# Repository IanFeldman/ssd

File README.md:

# ssd
2025 Cal Poly EE/CPE senior project exploring nonvolatile flash storage. Includes a [prototype design](#nor-prototype-2) using an 8051 and small NOR flash IC and the [final design](#nand-final) with a modern Atmel microcontroller and multiple high-density NAND flash ICs on a custom PCB.

## nand-final
2Gib NAND flash memory board with virtual serial interface over USB. Supports default and RAID 1 configurations.

### Firmware Build and Flash Instructions (Linux)
```sh
# Install dependencies
sudo apt install gcc-avr avr-libc avrdude make

# Clone this repo
git clone https://github.com/IanFeldman/ssd.git
cd ssd/nand-final/firmware

# Burn fuses (first time only)
make fuses

# Compile and flash firmware using ISP
# (edit makefile as needed)
make [UART=1] [RAID=1] # Optionally enable UART debugging or RAID 1
make flash
```

UART debugging interferes with some NAND chip control lines. Enable it at your own risk.\
RAID is performed across all 4 chips, so it decreases the address space fourfold.

### Usage:
Plug PCB into PC USB port and open a terminal with:\
```screen /dev/[path-to-usb-device] -b 9600```

### Commands:
<table>

<tr>
<td>Command</td>
<td>Usage</td>
<td>Function</td>
</tr>
<tr>
<td>Help</td>
<td>
  
```help```
</td>
<td>Displays device info and a list of commands.</td>
</tr>
<tr>
<td>Read</td>
<td>
  
```read 0x[row] 0x[column] [size]```
</td>
<td>Reads [size] bytes from memory.<br>A device will not read across a page boundary.</td>
</tr>
<tr>
<td>Write</td>
<td>
  
```write 0x[row] 0x[column] 0x[data]```
</td>
<td>Writes a single byte [data] to memory.</td>
</tr>
<tr>
<td>Erase</td>
<td>
  
```erase 0x[row]```
</td>
<td>Erases a block from memory.</td>
</tr>
</table>

Note:
- ```[row]``` is three bytes and represents a page address. Max value: 0x0FFFFF (0x040000 with RAID enabled).
- ```[column]``` is two bytes and represents a page offset in bytes. Max value: 0x07FF.
- ```[data]``` is one byte.
- ```[size]``` is a decimal unsigned integer.

## nor-prototype-2
Prototype breadboard 512kB flash memory storage device. Interface over UART at 9600 baud. Compile with SDCC and program with avrdude. See hardware schematic for hardware details.

### Firmware Build and Flash Instructions (Linux)
```sh
# Install dependencies
sudo apt install sdcc

# Clone this repo
git clone https://github.com/IanFeldman/ssd.git
cd ssd/nor-prototype-2/firmware

# Compile and flash firmware using ISP
make
./program.sh
```

### Usage:
Connect a serial cable to ```RXD``` and ```TXD``` on the microcontroller. Open a terminal with:\
```screen /dev/[path-to-serial-cable] -b 9600```

### Commands:
- Read an address ```r[address]```
- Erase an address ```e[address]```
- Program an address ```p[address][data]```

Where:
- ```[address]``` is 3 hex bytes
- ```[data]``` is one hex byte

## nor-prototype-1
Flash memory controller prototype.

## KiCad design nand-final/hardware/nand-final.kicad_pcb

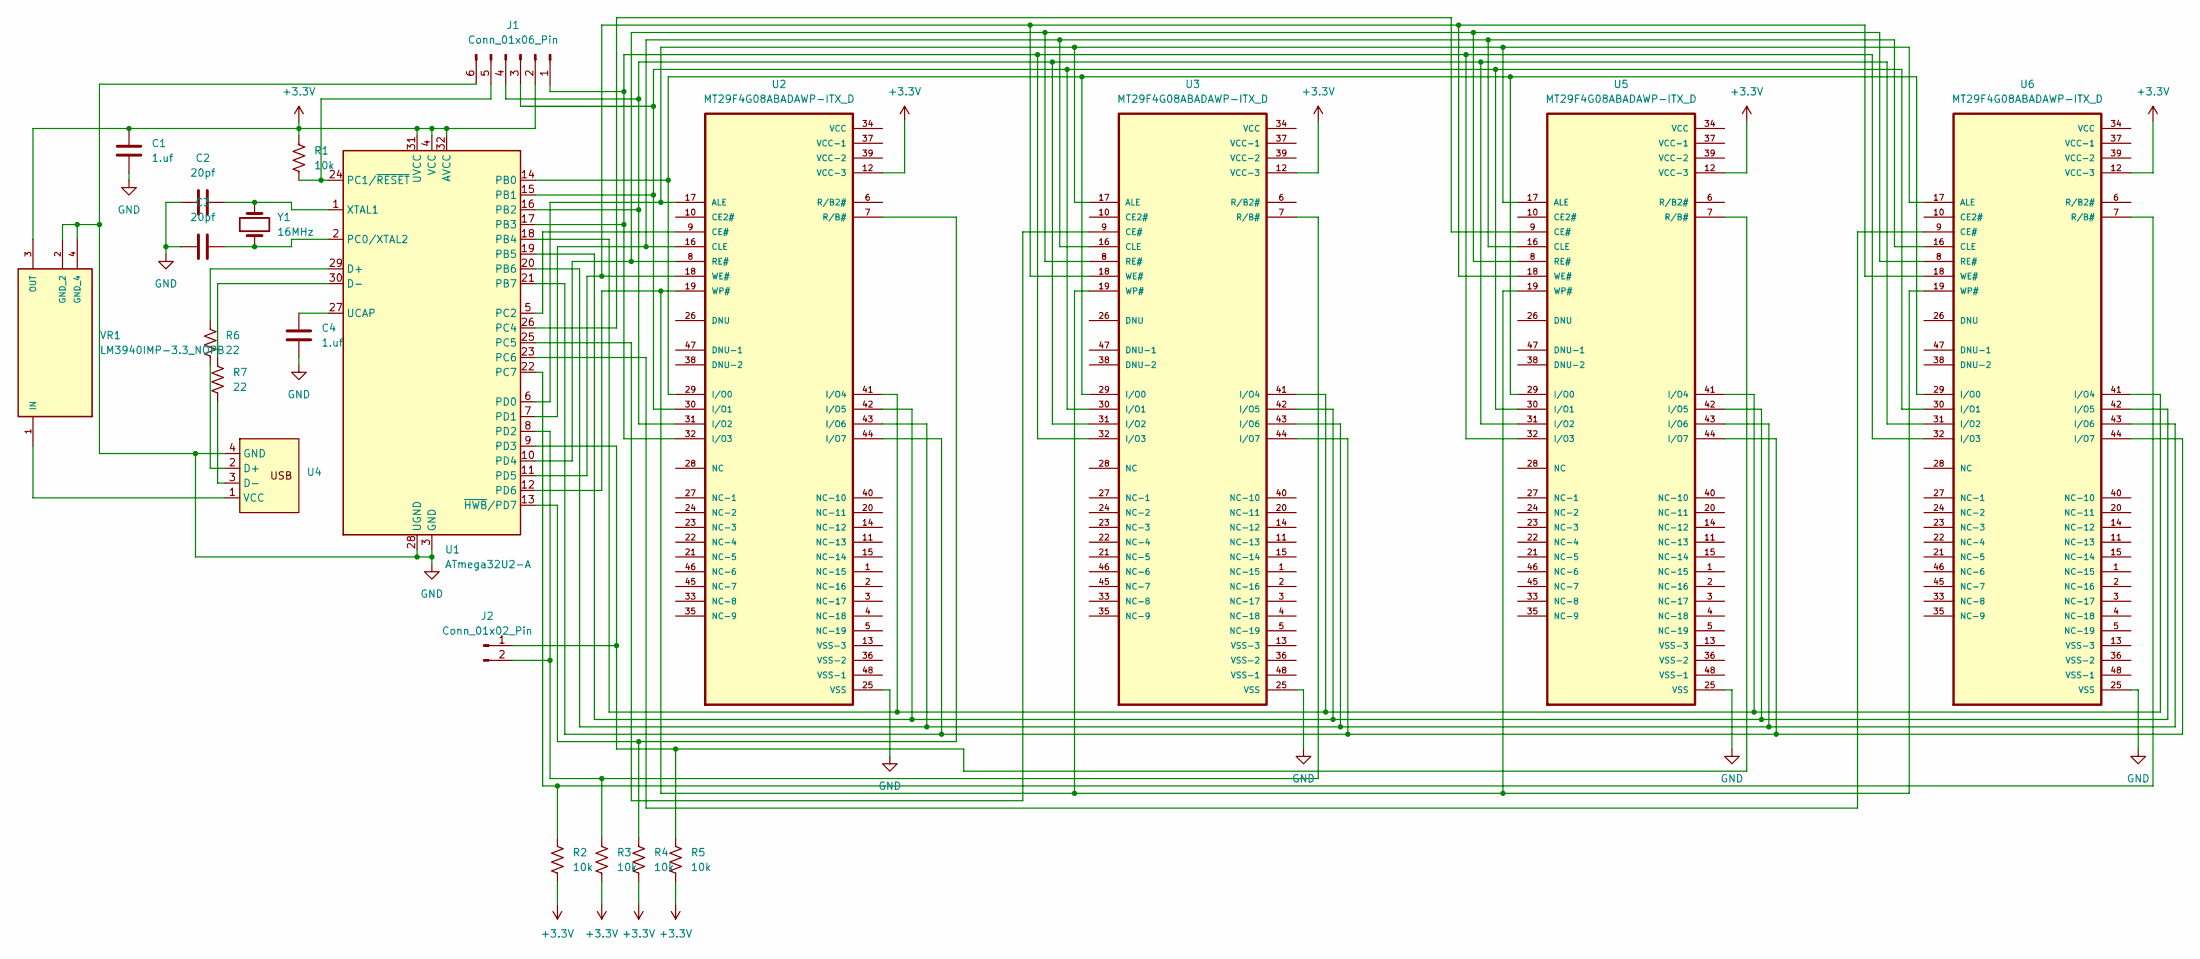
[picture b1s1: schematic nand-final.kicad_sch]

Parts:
C1, C4: 1.uf; C_0805_2012Metric_Pad1.18x1.45mm_HandSolder
C2, C3: 20pf; C_0805_2012Metric_Pad1.18x1.45mm_HandSolder
J1: Conn_01x06_Pin; PinHeader_1x06_P2.54mm_Vertical
J2: Conn_01x02_Pin; PinHeader_1x02_P2.54mm_Vertical
R1, R2, R3, R4, R5: 10k; R_0805_2012Metric_Pad1.20x1.40mm_HandSolder
R6, R7: 22; R_0805_2012Metric_Pad1.20x1.40mm_HandSolder
U1: ATmega32U2-A; TQFP-32_7x7mm_P0.8mm
U2, U3, U5, U6: MT29F4G08ABADAWP-ITX_D; TSOP-I-48_18.4x12mm_P0.5mm
U4: PCB_USB_connector
VR1: LM3940IMP-3.3_NOPB; SOT-223; PARTREV G
Y1: 16MHz; Crystal_HC49-U_Vertical

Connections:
+3.3V: C1.2, J1.2, R1.1, R2.2, R3.2, R4.2, R5.2, U1.4 (VCC), U1.31 (UVCC), U1.32 (AVCC), U2.12 (VCC-3), U3.12 (VCC-3), U5.12 (VCC-3), U6.12 (VCC-3), VR1.3 (OUT)
GND: C1.1, C2.2, C3.2, C4.1, J1.6, U1.3 (GND), U1.28 (UGND), U2.25 (VSS), U3.25 (VSS), U4.4 (GND), U5.25 (VSS), U6.25 (VSS), VR1.2 (GND_2), VR1.4 (GND_4)
unnamed: J1.1, U1.17 (PB3), U2.32 (I/O3), U3.32 (I/O3), U5.32 (I/O3), U6.32 (I/O3)
unnamed: J1.3, U1.15 (PB1), U2.30 (I/O1), U3.30 (I/O1), U5.30 (I/O1), U6.30 (I/O1)
unnamed: J1.4, U1.16 (PB2), U2.31 (I/O2), U3.31 (I/O2), U5.31 (I/O2), U6.31 (I/O2)
unnamed: J1.5, R1.2, U1.24 (PC1/~RESET)
unnamed: J2.1, R5.1, U1.9 (PD3), U5.7 (R/B#)
unnamed: J2.2, R3.1, U1.8 (PD2), U3.7 (R/B#)
unnamed: R6.1, U1.29 (D+)
unnamed: R7.1, U1.30 (D-)
unnamed: U1.14 (PB0), U2.29 (I/O0), U3.29 (I/O0), U5.29 (I/O0), U6.29 (I/O0)
unnamed: U1.18 (PB4), U2.41 (I/O4), U3.41 (I/O4), U5.41 (I/O4), U6.41 (I/O4)
unnamed: U1.19 (PB5), U2.42 (I/O5), U3.42 (I/O5), U5.42 (I/O5), U6.42 (I/O5)
unnamed: U1.20 (PB6), U2.43 (I/O6), U3.43 (I/O6), U5.43 (I/O6), U6.43 (I/O6)
unnamed: U1.21 (PB7), U2.44 (I/O7), U3.44 (I/O7), U5.44 (I/O7), U6.44 (I/O7)
unnamed: C3.1, U1.2 (PC0/XTAL2), Y1.1
unnamed: U1.5 (PC2), U2.9 (CE#)
unnamed: U1.26 (PC4), U5.9 (CE#)
unnamed: U1.25 (PC5), U3.9 (CE#)
unnamed: U1.23 (PC6), U6.9 (CE#)
unnamed: R2.1, U1.22 (PC7), U6.7 (R/B#)
unnamed: U1.6 (PD0), U2.17 (ALE), U3.17 (ALE), U5.17 (ALE), U6.17 (ALE)
unnamed: U1.7 (PD1), U2.16 (CLE), U3.16 (CLE), U5.16 (CLE), U6.16 (CLE)
unnamed: U1.10 (PD4), U2.8 (RE#), U3.8 (RE#), U5.8 (RE#), U6.8 (RE#)
unnamed: U1.11 (PD5), U2.18 (WE#), U3.18 (WE#), U5.18 (WE#), U6.18 (WE#)
unnamed: U1.12 (PD6), U2.19 (WP#), U3.19 (WP#), U5.19 (WP#), U6.19 (WP#)
unnamed: C4.2, U1.27 (UCAP)
unnamed: C2.1, U1.1 (XTAL1), Y1.2
unnamed: R4.1, U1.13 (~HWB/PD7), U2.7 (R/B#)
unnamed: R6.2, U4.2 (D+)
unnamed: R7.2, U4.3 (D-)
unnamed: U4.1 (VCC), VR1.1 (IN)

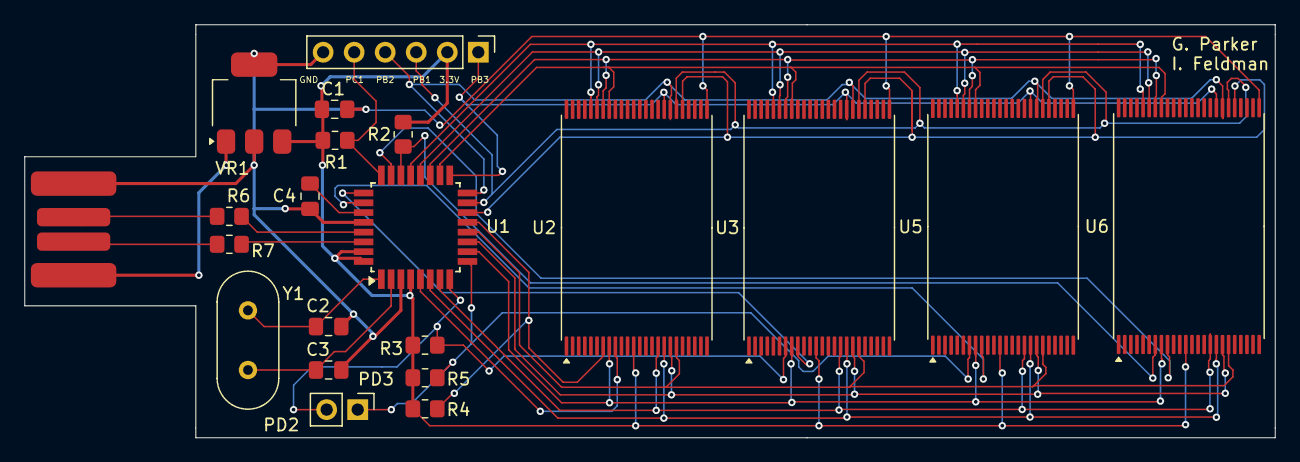
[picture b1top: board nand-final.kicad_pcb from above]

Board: 2 copper layers, 102.3 x 33.8 mm, 21 parts (0 on the bottom side), 32 nets.

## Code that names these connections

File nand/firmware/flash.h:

#ifndef FLASH_H
#define FLASH_H

#include <stdio.h>

#define F_CPU 16000000UL
#define CHIP_COUNT 4

/* port c, active low, outputs */
#define CHIP_ENABLE_1     (1 << PC2)
#define CHIP_ENABLE_2     (1 << PC5)
#define CHIP_ENABLE_3     (1 << PC4)
#define CHIP_ENABLE_4     (1 << PC6)
#define CHIP_ENABLE_DIR_1 (1 << DDC2)
#define CHIP_ENABLE_DIR_2 (1 << DDC5)
#define CHIP_ENABLE_DIR_3 (1 << DDC4)
#define CHIP_ENABLE_DIR_4 (1 << DDC6)

/* port c/d, active low, inputs (external pull up) */
#define READY_BUSY_1     (1 << PD7)
#define READY_BUSY_2     (1 << PD2)
#define READY_BUSY_3     (1 << PD3)
#define READY_BUSY_4     (1 << PC7)
#define READY_BUSY_DIR_1 (1 << DDD7)
#define READY_BUSY_DIR_2 (1 << DDD2)
#define READY_BUSY_DIR_3 (1 << DDD3)
#define READY_BUSY_DIR_4 (1 << DDC7)

/* port d outputs */
#define ADDR_LATCH       (1 << PD0) /* active high */
#define CMD_LATCH        (1 << PD1) /* active high */
#define READ_ENABLE      (1 << PD4) /* active low  */
#define WRITE_ENABLE     (1 << PD5) /* active low  */
#define WRITE_PROT       (1 << PD6) /* active low  */
#define ADDR_LATCH_DIR   (1 << DDD0)
#define CMD_LATCH_DIR    (1 << DDD1)
#define READ_ENABLE_DIR  (1 << DDD4)
#define WRITE_ENABLE_DIR (1 << DDD5)
#define WRITE_PROT_DIR   (1 << DDD6)

/* commands */
#define RESET_CMD            0xFF
#define READ_ID_CMD          0x90
#define READ_PAGE_CMD        0x00
#define END_READ_PAGE_CMD    0x30
#define RANDOM_READ_CMD      0x05
#define END_RANDOM_READ_CMD  0xE0
#define PROGRAM_PAGE_CMD     0x80
#define END_PROGRAM_PAGE_CMD 0x10
#define ERASE_BLOCK_CMD      0x60
#define END_ERASE_BLOCK_CMD  0xD0

void flash_init();
void flash_enable(int chip);
void flash_disable(int chip);
void flash_read_id(uint8_t *id, int chip);
uint8_t flash_read(uint32_t address, uint16_t column, int chip);
void flash_program(uint32_t address, uint16_t column,
    uint8_t *data, int size, int chip);
void flash_erase(uint32_t address, int chip);

#endif /* FLASH_H */

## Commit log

2025-02-05 Init commit
2025-02-05 Create Makefile, clean uart init
2025-02-05 Create print function
2025-02-05 Add hardware schematic
2025-02-06 Support ANSI escape codes, refactor uart code
2025-02-06 Fix uart print error handling
2025-02-07 Implement flash read
2025-02-08 Implement flash program, rename flash.sh
2025-02-08 Begin implementing SDP
2025-02-08 Add variable delay
2025-02-09 Get data from serial interrupts
2025-02-09 Remove compilation outputs
2025-02-09 Add sdp function, implement flash_erase
2025-02-09 Fix control pins, create get_id()
2025-02-10 Fix set_address(), delete useless code
2025-02-10 Update schematic with pull ups for port 0
2025-02-10 Remove random line from schematic
2025-02-14 Add time delay to flash operations
2025-02-14 Increase time for flash erase
2025-02-14 Optimize memory overhead of uart
2025-02-14 Optimize memory overhead of flash
2025-02-14 Begin handling user input buffer
2025-02-14 Create parse_input function
2025-02-14 Remove string.h dependency
2025-02-18 Implement cmd line read
2025-02-18 Implement cmd line program
2025-02-18 Add print address function
2025-02-18 Change nand to nor in makefile
2025-02-18 Implement cmd line erase
2025-02-18 Cap print address function at max address
2025-02-18 Update erase message
2025-02-18 Fix handle unknown input
2025-02-21 Reorganize into nand and nor folders
2025-02-24 Change crystal capacitors
2025-02-28 Take device measurements
2025-03-17 Create initial nand firmware
2025-03-17 Add uart
2025-03-17 Configure uart for hello world
2025-03-17 Update schematic
2025-04-05 Flash init
2025-04-05 Flash read id
2025-04-09 Change to multi data read
2025-04-09 Update program scripts
2025-04-09 Change delays, read bytes
2025-04-09 Fix read
2025-04-10 Organize
2025-04-10 Update flash read
2025-04-10 Comments
2025-04-11 Single byte read+write
2025-04-15 Add LUFA for USB support
2025-04-15 Replace led debug with uart debug
2025-04-15 Incorporate shell scripts into makefile
2025-04-15 Clean up
2025-05-14 Create test branch
2025-05-15 Fix fuses
2025-05-15 Support four nand chips
2025-05-15 Issue reset to all chips
2025-05-15 Add chip enable/disable
2025-05-15 Print new line
2025-05-15 Add block erase
2025-05-15 Increase delay timing
2025-05-15 Increase delays
2025-05-15 Test all chips
2025-05-16 Properly name address
2025-05-20 Clean make warnings
2025-05-20 Fix make issues
2025-05-20 Rename to lower case
2025-05-20 Convert tabs to spaces
2025-05-20 Purge unnecessary lufa files
2025-05-20 Add comments and clean up
2025-05-20 Add hardware
2025-05-20 Remove old schematic
2025-05-21 Consider ftl
2025-05-23 Calculate write block addresses
2025-05-25 ISP connections
2025-05-28 Work on write blocks
2025-05-29 Update flash address write calculations
2025-06-09 Add 3d model
2025-06-10 Change to block interfacing
2025-06-10 Fake boot sector
2025-06-10 Change to virtual serial
2025-06-10 Poll for input
2025-06-10 Remove unnecessary LUFA files
2025-06-10 Develop shell
2025-06-10 Shell progress
2025-06-10 Read command
2025-06-10 Finish read command
2025-06-10 Write command
2025-06-10 Erase command
2025-06-10 Check lengths and write help
2025-06-10 Shorten help, convert to 0x inputs
2025-06-10 Check hex prefixes
2025-06-10 Add boundary checking
2025-06-11 Add uart define
2025-06-11 Implement RAID 1
2025-06-11 Change chip_row to uint32
2025-06-11 Add debug timing pin
2025-06-11 Nand characterization
2025-06-11 Upload nor prototype
2025-06-11 Add schematic images
2025-06-11 Rename folders
2025-06-11 Change comments
2025-06-11 Memory safe reads
